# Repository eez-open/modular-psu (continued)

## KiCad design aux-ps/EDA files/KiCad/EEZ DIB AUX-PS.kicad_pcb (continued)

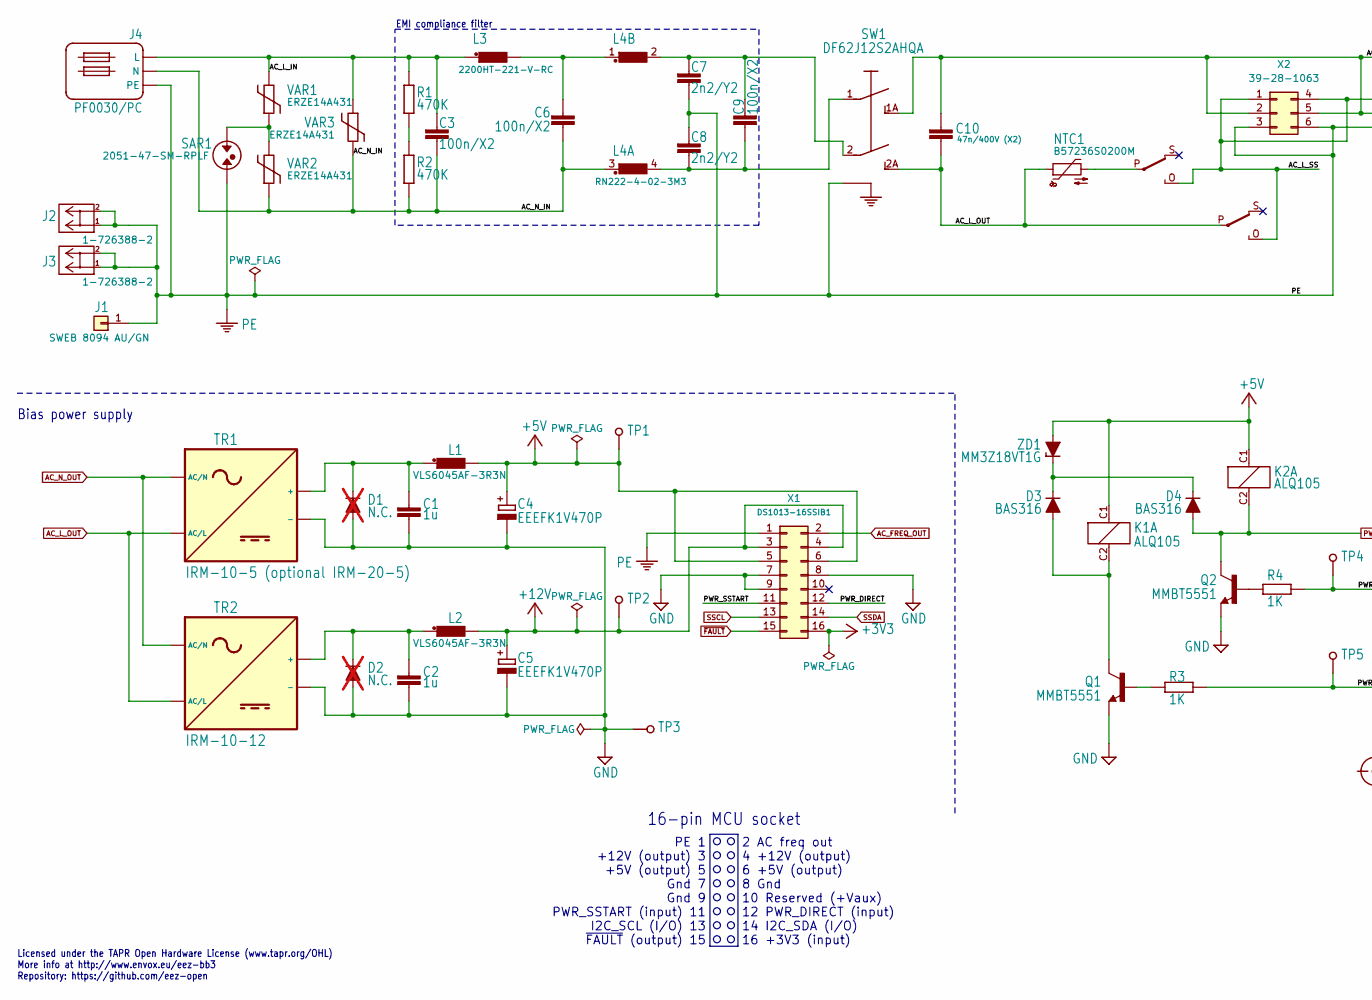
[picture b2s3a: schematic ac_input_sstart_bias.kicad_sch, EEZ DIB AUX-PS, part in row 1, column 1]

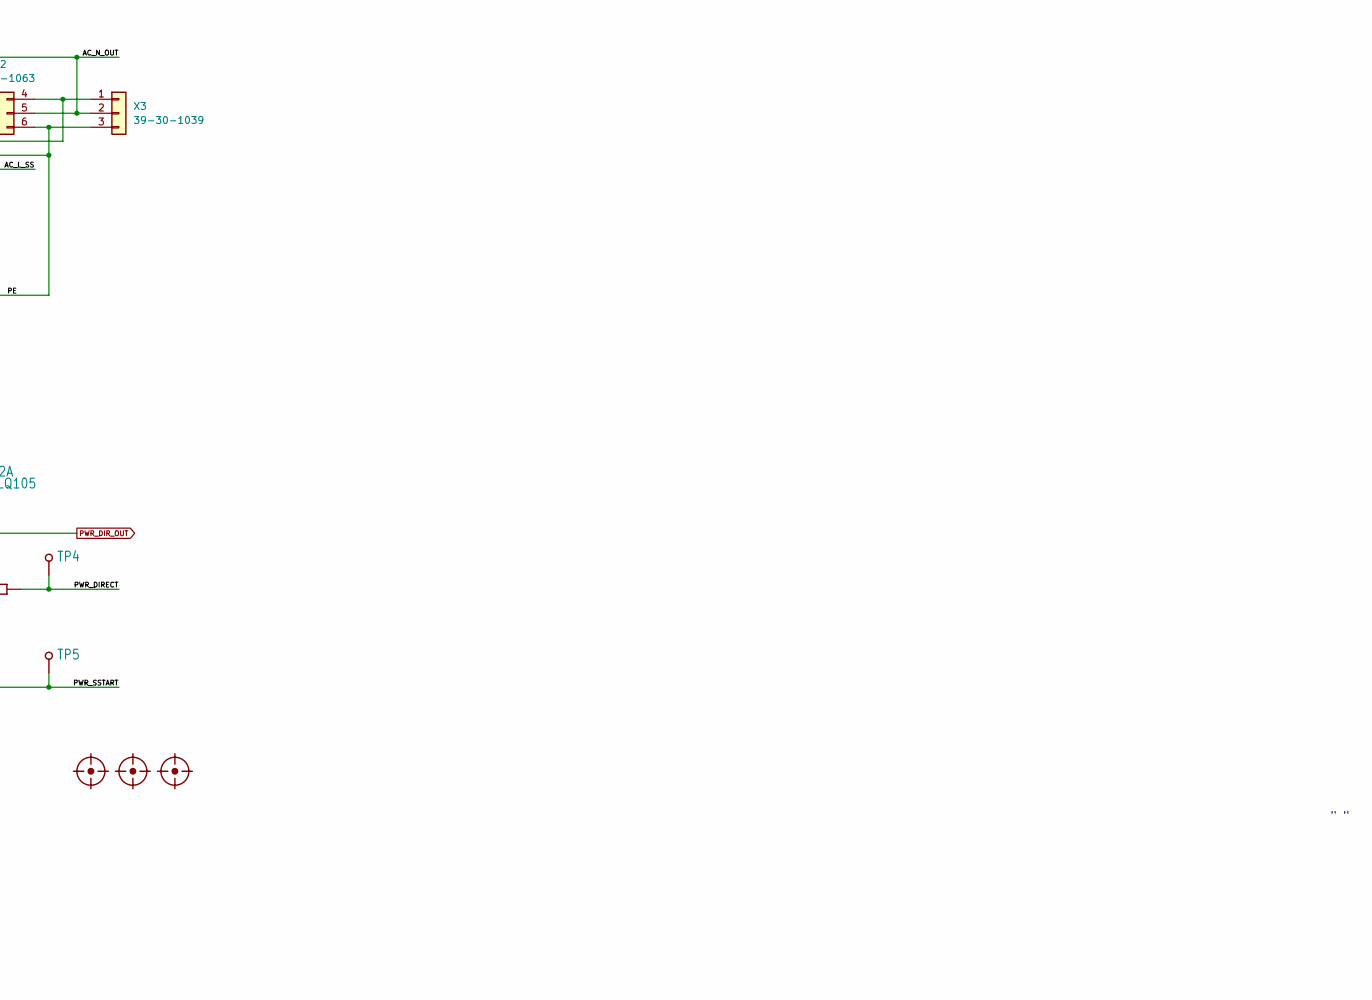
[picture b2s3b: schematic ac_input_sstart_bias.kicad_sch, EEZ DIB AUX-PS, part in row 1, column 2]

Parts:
C1, C2: 1u; C_0805_2012Metric; DigiKey 490-10494-2-ND
C3, C6, C9: 100n/X2; C150-054X183; DigiKey 399-6806-ND
C4, C5: EEEFK1V470P; CAPAE660X610N; DigiKey PCE3842CT-ND
C7, C8: 2n2/Y2; C075-042X103; DigiKey 495-4874-1-ND
C10: 47n/400V (X2); C102-054X133; DigiKey 399-11478-ND
D1, D2: N.C.; DO214AA; not fitted
D3, D4: BAS316; SOD-323_1P8X1P35_ONS-M; DigiKey 1727-7370-1-ND
FM1, FM2, FM3: FIDUCIAL; Fiducial
J1: SWEB 8094 AU/GN; SWEB 8094_AU_GN
J2, J3: 1-726388-2; DigiKey 1-726388-2-ND
J4: PF0030/PC; PF0030_PC; DigiKey 708-1914-ND
K1, K2: ALQ105; PAN_ALQ1XX; DigiKey 255-3565-ND
L1, L2: VLS6045AF-3R3N; COILCRAFT_HPI0630; DigiKey 445-180834-1-ND
L3: 2200HT-221-V-RC; BOURNS_2200; DigiKey 2200HT-221-V-RC-ND
L4: RN222-4-02-3M3; BOURNS_7100_COMBO; DigiKey 817-2100-ND
NTC1: B57236S0200M; NTC_11.5X6_RM5; DigiKey 495-3047-ND
Q1, Q2: MMBT5551; SOT23-BEC; DigiKey 4878-MMBT5551CT-ND
R1, R2: 470K; R_0805_2012Metric; DigiKey A126370CT-ND
R3, R4: 1K; R_0805_2012Metric; DigiKey 311-1.00KCRTR-ND
SAR1: 2051-47-SM-RPLF; SAR_4.5MM; DigiKey 2051-47-SM-RPLFCT-ND
SW1: DF62J12S2AHQA; DF62J12S2; DigiKey CKN2062-ND
TP1, TP2, TP3, TP4, TP5: PCB_TEST_TABSHIELD; Testhole 24_50mils
TR1: IRM-10-5 (optional IRM-20-5); IRM-10_20_COMBO; DigiKey 1866-3032-ND
TR2: IRM-10-12; IRM-10; DigiKey 1866-3028-ND
VAR1, VAR2, VAR3: ERZE14A431; VARISTOR_14MM_RM7.5MM; DigiKey P16688-ND
X1: DS1013-16SSIB1; ZL231-16PG; DigiKey ED10523-ND
X2: 39-28-1063; MINIFIT_5566-06A_CRE; DigiKey WM3802-ND
X3: 39-30-1039; MINIFIT_39301039_CRE; DigiKey WM18442-ND
ZD1: MM3Z18VT1G; SOD-323_1P8X1P35_ONS-M; DigiKey MM3Z18VT1GOSCT-ND

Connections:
+3V3: X1.16; also elsewhere on the board
+5V: C4.+, K1.C1, K2.C1, L1.2, TP1.1, X1.5, X1.6, ZD1.A; also elsewhere on the board
+12V: C5.+, L2.2, TP2.1, X1.3, X1.4; also elsewhere on the board
/AC input, soft start and bias power/AC_L_IN: C3.1, J4.L, L3.1, R1.2, VAR1.2, VAR3.1
/AC input, soft start and bias power/AC_L_SS: K1.O, K2.O, X2.1, X2.4, X3.1
/AC input, soft start and bias power/AC_N_IN: C3.2, C6.2, J4.N, L4.3 (1), R2.1, VAR2.1, VAR3.2
/AC input, soft start and bias power/PWR_DIRECT: R4.2, TP4.1, X1.12
/AC input, soft start and bias power/PWR_SSTART: R3.2, TP5.1, X1.11
AC_FREQ_OUT: X1.2; also elsewhere on the board
AC_L_OUT: C10.2, K2.P, NTC1.1, SW1.2A (S1), TR1.ACL (AC/L), TR2.ACL (AC/L); also elsewhere on the board
AC_N_OUT: C10.1, SW1.1A (S), TR1.ACN (AC/N), TR2.ACN (AC/N), X2.2, X2.5, X3.2; also elsewhere on the board
GND: C1.2, C2.2, C4.-, C5.-, D1.A, D2.A, Q1.E, Q2.E, TP3.1, TR1.V- (-), TR2.V- (-), X1.7, X1.8, X1.9; also elsewhere on the board
unnamed: C6.1, L3.2, L4.1
unnamed: D3.A, K1.C2, Q1.C
unnamed: D3.C, D4.C, ZD1.C
unnamed: K1.P, NTC1.2
unnamed: C8.2, C9.1, L4.4 (2), SW1.1
unnamed: Q1.B, R3.1
unnamed: Q2.B, R4.1
unnamed: R1.1, R2.2
unnamed: SAR1.1, VAR1.1, VAR2.2
unnamed: C7.1, C9.2, L4.2, SW1.2 (P1)
unnamed: C1.1, D1.C, L1.1, TR1.V+ (+)
unnamed: C2.1, D2.C, L2.1, TR2.V+ (+)
PE: C7.2, C8.1, J1.1, J2.1, J2.2, J3.1, J3.2, J4.PE, SAR1.2, SW1.PE, X1.1, X2.3, X2.6, X3.3; also elsewhere on the board
PWR_DIR_OUT: D4.A, K2.C2, Q2.C; also elsewhere on the board
SSCL: X1.13; also elsewhere on the board
SSDA: X1.14; also elsewhere on the board
~FAULT: X1.15; also elsewhere on the board

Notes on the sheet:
2 AC freq out 4 +12V (output) 6 +5V (output) 8 Gnd 10 Reserved (+Vaux) 12 PWR_DIRECT (input) 14 I2C_SDA (I/O) 16 +3V3 (input)
PE 1 +12V (output) 3 +5V (output) 5 Gnd 7 Gnd 9 PWR_SSTART (input) 11 I2C_SCL (I/O) 13 ~{FAULT} (output) 15
EMI compliance filter
" "
Bias power supply
16-pin MCU socket
Licensed under the TAPR Open Hardware License (www.tapr.org/OHL) More info at http://www.envox.eu/eez-bb3 Repository: https://github.com/eez-open

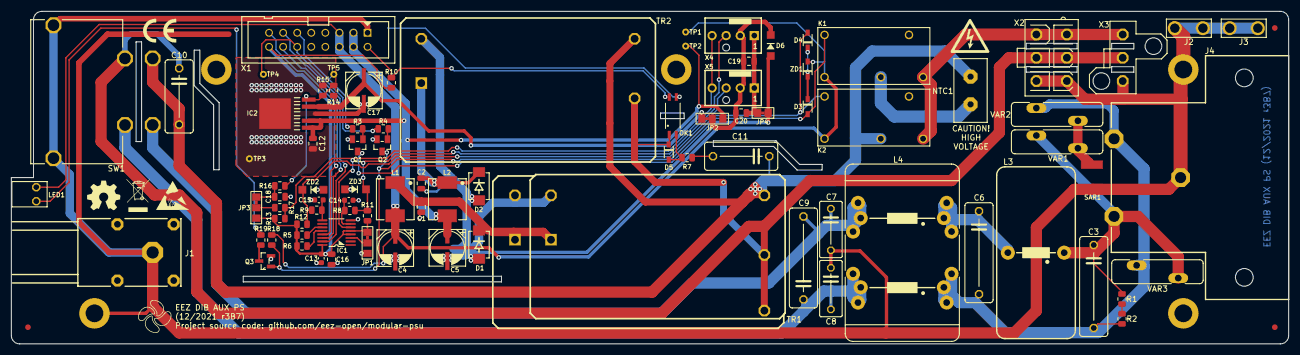
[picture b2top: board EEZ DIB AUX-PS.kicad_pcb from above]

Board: 2 copper layers, 230.5 x 60.0 mm, 101 parts (0 on the bottom side), 47 nets.

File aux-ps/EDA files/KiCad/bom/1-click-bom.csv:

References,Qty,Description,Manufacturer,MPN,Manufacturer,MPN,Manufacturer,MPN,DigiKey,Mouser,TME
"C1, C2, C16, C18, C19",5,1u,,490-10494-2-ND,,81-GRM219R7YA105KA2J,,GRM219R7YA105KA12D,,,
C10,1,47n/400V (X2),,399-11478-ND,,871-B32921C3473K,,MKP-X2-47NR10/310,,,
"C13, C14",2,100n,,1276-1005-2-ND,,187-CL10B104KO8NNNC ,,CL10B104KA8NNNC,,,
"C3, C6, C9",3,100n/X2,,399-6806-ND ,,80-R46KI310000M1M,,R46KI310000M1M,,,
"C4, C5, C17",3,EEEFK1V470P,,PCE3842CT-ND,,667-EEE-FK1V470P,,EEEFK1V470P,,,
"C7, C8",2,2n2/Y2,,495-4874-1-ND,,871-B32620A6222J289,,R66PD1220AA10K,,,
"D3, D4",2,BAS316,,1727-7370-1-ND,,771-BAS316-T/R,,"BAS316,115",,,
D6,1,SKL14,,1727-7335-1-ND,,841-PMEG4010EGWX,,SKL14-DIO,,,
IC1,1,MAX31760AEE+,,MAX31760AEE+-ND ,,700-MAX31760AEE+,,-,,,
IC2,1,BD00FC0W,,BD00FC0WFP-E2TR-ND,,755-BD00FC0WFP-E2,,-,,,
J1,1,SWEB 8094 AU/GN,,-,,-,,SWEB 8094 AU/GN,,,
"J2, J3",2,1-726388-2,,1-726388-2-ND,,571-1-726388-2,,61-1560-21/0030,,,
J4,1,PF0030/PC,,708-1914-ND,,161-PF0030/PC,,PF0030/PC,,,
"K1, K2",2,ALQ105,,255-3565-ND,,769-ALQ105,,ALQ105,,,
"L1, L2",2,VLS6045AF-3R3N,,445-180834-1-ND,,810-VLS6045AF-3R3N,,HPI0630-3R3,,,
L3,1,2200HT-221-V-RC,,2200HT-221-V-RC-ND,,542-2200HT-221V-RC,,-,,,
L4,1,RN222-4-02-3M3,,817-2100-ND,,631-RN112-4-02-0M7,,-,,,
LED1,1,WP934CB/YD,,754-1300-ND,,604-WP934CB/YD ,,L-934CB/1YD,,,
NTC1,1,B57236S0200M,,495-3047-ND ,,871-B57236S200M,,B57236S0200,,,
"Q1, Q2",2,MMBT5551,,4878-MMBT5551CT-ND,,863-MMBT5551LT1G,,MMBT5551-7-F,,,
Q3,1,2N7002,,T2N7002AKLMCT-ND,,757-T2N7002AKLM,,2N7002LT1G,,,
"R1, R2",2,470K,,A126370CT-ND,,71-CRCW0805470KFKEA,,0805S8J0474T5E,,,
"R14, R18",2,39K,,RMCF0805FT39K0CT-ND,,652-CR0805FX-3902ELF,,0805S8J0393T5E,,,
"R15, R16",2,3K3,,A129755CT-ND,,603-RC0805FR-073K3L,,805S8F3301T5E,,,
R19,1,470R,,311-470CRCT-ND,,71-CRCW0805470RFKEB,,RC0805FR-07470R,,,
"R3, R4, R11, R12, R17",5,1K,,311-1.00KCRTR-ND,,603-RC0805FR-071KL,,RC0805FR-071K,,,
"R5, R13",2,4K7,,311-4.70KCRCT-ND,,603-RC0805FR-074K7L,,0805S8F4701T5E,,,
R8,1,10R,,311-10.0CRTR-ND,,652-CR0805AFX10R0EAS,,SMD0805-10R-1%,,,
SAR1,1,2051-47-SM-RPLF,,2051-47-SM-RPLFCT-ND,,652-2051-47-SM-RPLF,,-,,,
SW1,1,DF62J12S2AHQA,,CKN2062-ND,,611-DF62J12S2AHQA,,DF62J12S2AHQA,,,
TR1,1,IRM-10-5 (optional IRM-20-5),,1866-3032-ND,,709-IRM10-5 ,,IRM-10-5,,,
TR2,1,IRM-10-12,,1866-3028-ND ,,709-IRM10-12 ,,IRM-10-12,,,
"VAR1, VAR2, VAR3",3,ERZE14A431,,P16688-ND,,667-ERZ-E11A431,,V275LA20AP,,,
X1,1,DS1013-16SSIB1,,ED10523-ND,,710-61201621621,,DS1013-16SSIB1,,,
X2,1,39-28-1063,,WM3802-ND,,538-39-28-1063,,MX-5566-06A,,,
X3,1,39-30-1039,,WM18442-ND ,,538-39-30-1039 ,,MX-5566-03A3,,,
X4,1,22-27-2031,,WM4112-ND,,538-22-27-2031,,MX-6410-03A,,,
ZD1,1,MM3Z18VT1G,,MM3Z18VT1GOSCT-ND,,863-MM3Z18VT1G,,MM3Z18VT1G,,,

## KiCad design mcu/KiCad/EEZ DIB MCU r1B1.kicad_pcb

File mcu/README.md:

### Overview

_IMPORTANT: A crowdfunded version of the MCU module (r2B4) can be found [here](https://github.com/eez-open/modular-psu/tree/master/previous%20designs/mcu%20r2B4%20(Crowd%20Supply%20edition))._

STM32F7 MCU board for controlling up to 3 SPI peripheral modules, I2C fan controller, power soft-start/standby, TFT LCD with resistive touch controller, USB OTG, 10/100 Mbit/s Ethernet, SDRAM, EEPROM, rotary encoder, user switch, speaker and 2+2 digital I/O.

### r3B3 prototype

### Feature list

* [STM32F769IIT6](https://www.st.com/content/st_com/en/products/microcontrollers-microprocessors/stm32-32-bit-arm-cortex-mcus/stm32-high-performance-mcus/stm32f7-series/stm32f7x9/stm32f769ii.html) 32-bit ARM Cortex®-M7 MCU, 216 MHz, 2 MiB Flash, 512 KiB SRAM,  LQFP176 package
* Digital I/O: 2 x buffered inputs and 2 x buffered outputs. Alternative functions: UART, 1 x PWM
* Rotary encoder with switch
* 1 x user switch (use as BOOT0 for firmware loader on power up)
* 3 x SPI channels (2 x Chip selects per channel), 40-pin IDC connector (DIB v1.0)
* Battery backup (CR2032 button cell type)
* AC frequency (50/60 Hz) RTC reference (optional)
* External supervisor with watchdog (optional)
* USB FS, OTG
* Micro SD card
* [DP83848C](https://www.ti.com/product/DP83848C) Ethernet PHY (10/100 Mbit/s)
* 32 KiB I2C EEPROM
* SWG/JTAG connector (optional)
* 8 MiB SDRAM (e.g. [IS42S16400J](https://www.tme.eu/en/details/is42s16400j-7tli/dram-memories-integrated-circuits/issi/)) upgradeable to 32 MiB
* 0.5 mm FFC 40-pin connector for 4.3" TFT LCD 480 x 272 px display
* TFT backlight brightness control
* Resistive touch controller (I2C)
* Soft-start/stand-by control lines for [AUX PS board](https://github.com/eez-open/modular-psu/tree/master/aux-ps)
* Small on-board speaker
* Input power: +5 V (+12 V pass-thru to peripheral modules)
* On board +3.3 V LDO
* Dimensions: 139.5 x 70 mm, 4-layer PCB
* **CE certified design**

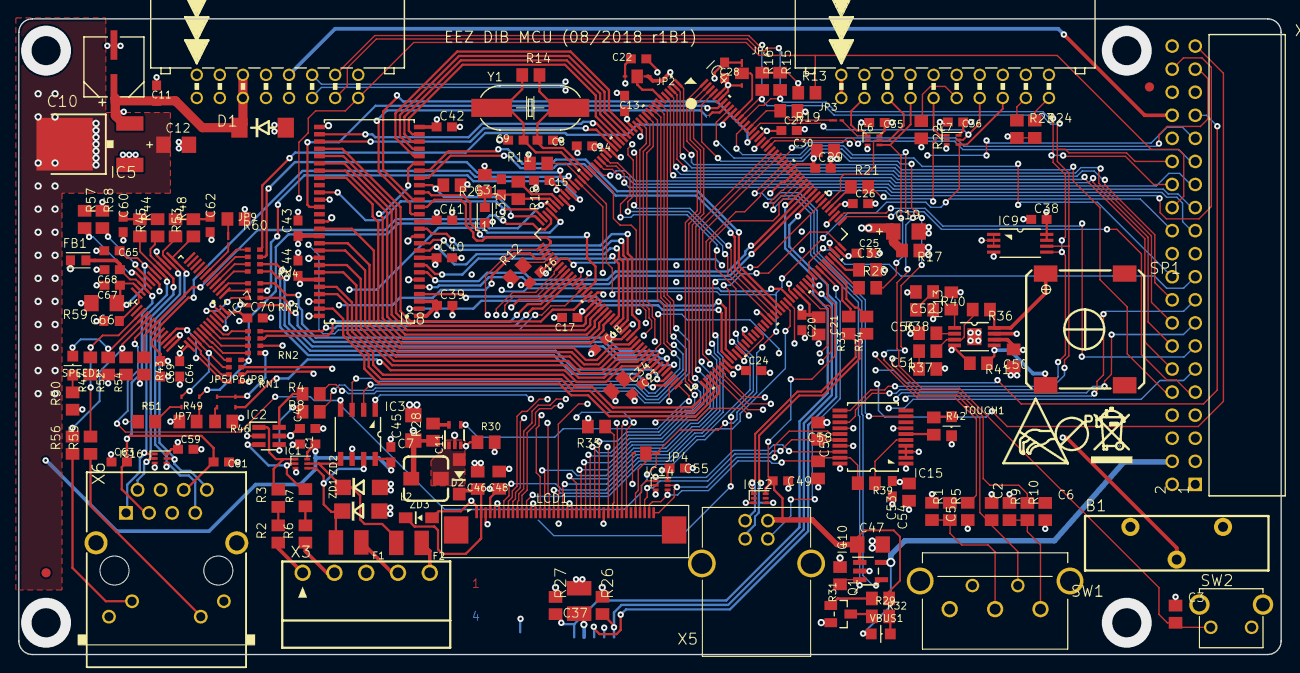
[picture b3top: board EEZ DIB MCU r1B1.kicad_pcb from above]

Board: 4 copper layers, 139.0 x 70.0 mm, 193 parts (0 on the bottom side), 233 nets.

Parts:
B1: DS1092-16-B6P
C1, C4, C7, C11, C13, C14, C15, C16, C17, C18, C20, C23, C24, C25, C26, C27, C28, C29, C32, C35, C36, C38, C39, C40, C41, C42, C43, C44, C49, C53, C55, C59, C60, C61, C62, C63, C64, C65, C67, C68, C69, C70: 100n; C0603
C2, C3, C5, C6, C57, C58: 10n; C0805
C8, C9: 18p; C0603
C10: 47u; CAPAE660X610N
C12, C66: 10u; EC1206
C19: 4u7; EC1206
C21, C30, C31, C46, C50, C54: 1u; C0805
C22: N.C.; C0603
C33, C34, C48: 2u2; C0805
C37: 10u; C1210
C45: 4u7; C1206
C47: 4u7/16V (293D475X9016A2TE3); EC1206
C51, C52: 470n; C0805
C56: 220n; C0805
D1: SMBJ5.0A-TR; DO214AA
D2: NSR0240; SOD123
EEZ_SIGNATURE: SIGNATURESMALL; SIGNATURE_5MM
F1, F2: 50mA; F1210
FB1: 60R@100MHz; BEAD0603
FM1, FM2: FIDUCIAL
IC1, IC6, IC7, IC12, IC14, IC16: TPD4E001DRLR; DRL6
IC2: SN74LVC2G34DBVR; DBV6
IC3: BTS3408G; SOIC127P600X173-8N
IC4: STM32F769IGT6; LQFP-176_24X24MM
IC5: LD1117ADT33TR; DPACK
IC8: IS42S16400J; TSOPII-54
IC9: BR24G64FVT-3AGE2; PW8_TSSOP8
IC10: TPS2051BDBVR; DBV5
IC11: TPS61169DCKR; DCK5
IC13: TPA6205A1DGN; SOP65P490X110-9N
IC15: AR1021-I/SS; SOP65P780X200-20N
IC17: DP83848CVV_NOPB; PT48
J1: 5033981892
JP1, JP2, JP4: JP3-CUT
JP3, JP9: JP2-NOCUT
JP5, JP6, JP7, JP8: JP2-CUT
L1: LCBA-600; BEAD0603
L2: DLG-0403-4R7; DE0403
LCD1: PCA-6-LA-40-HL-3; FPC_40
Q1: MMBT5551; SOT23-BEC
R1, R2, R3, R6, R7, R9, R13, R15, R16, R42: 4K7; R0805
R4, R8: 1K; R0805
R5, R10, R11, R12, R22, R23, R24, R25, R35, R37, R38: 10K; R0805
R14: 1M; R0805
R17: 0R; R0805
R18: 47R; R0805
R19, R26, R27, R29, R31, R32, R40: 47K; R0805
R20, R21, R33, R34: 22R; R0805
R28, R30: 10R; R0805
R36, R39, R41: 20K; R0805
R43: 1K5; R0805
R44, R45, R48, R53: 49R9; R0805
R46, R47, R49, R51, R52, R54, R57, R58, R60: 2K2; R0805
R50, R55, R56: 220R; R0805
R59: 4K87; R0603
RN1, RN2, RN3, RN4: DR1206-33R-4/8; CAY16
SP1: LD-BZEL-M1313
SPEED1: HSMY-C170; LED_0805
SW1: PEC16-2215F-S0024; PEC16-2215F
SW2: BSF-3152; BSF-315X
TOUCH1: HSMY-C170; LED_0805
U$1: RECYCLE_BIN1_8
U$5: PB_SMALL
U$6: ESD_SYMBOL
VBUS1: HSMG-C170; LED_0805
X1: ZL263-40DG
X2: ZL231-16KG; ML16L
X3: 1844249; MC1,5_5-G-3,5
X4: ZL231-20KG; ML20L
X5: 292304-1; USB-B
X6: LMJTAB881243M-L; RJ45-TRAFO-LED
Y1: 10MHz; HC-49_4H
ZD1, ZD2: SMAJ18A; DO214AC
ZD3: BZX384-B30.115; SOD323-W

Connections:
+3V3: C4.1, C12.+, C35.1, C36.1, C37.1, C38.2, C39.1, C40.1, C41.1, C42.1, C43.1, C44.1, C45.1, C48.1, C50.2, C53.2, C54.2, C55.2, C59.1, C69.1, C70.1, FB1.P$1, IC2.5, IC5.4, IC6.6, IC7.6, IC8.1, IC8.3, IC8.9, IC8.14, IC8.27, IC8.43, IC8.49, IC9.1, IC9.2, IC9.3, IC9.7, IC9.8, IC13.6, IC14.6, IC15.1, IC16.6, IC17.32, IC17.48, J1.4, L2.1, LCD1.4, R1.1, R9.1, R13.1, R15.1, R16.1, R17.1, R19.1, R25.1, R26.1, R27.1, R28.1, R31.2, R35.2, R40.2, R43.2, R47.1, R50.1, R51.1, R52.1, R54.1, R57.1, R58.1, R60.1, X1.32, X2.16, X4.1, X4.2, X6.9, X6.12
+3V3(A): C61.2, C63.2, C68.1, FB1.P$2, IC17.22, X6.3, X6.6
+5V: C1.1, C7.2, C10.1, C11.1, D1.C, IC1.6, IC3.8, IC5.3, IC10.5, VBUS1.A, X1.3, X1.4, X2.5, X2.6
+12V: X1.5, X1.6, X2.3, X2.4
/Ethernet PHY/LED_ACT: IC17.26, R47.2, R55.2
/Ethernet PHY/LED_LINK: IC17.28, R54.2, R56.2
/Ethernet PHY/LED_SPEED: IC17.27, R52.2, SPEED1.C
/I/O connectors, encoders, user SW/+VAUX: X1.34, X2.10
/SDRAM, JTAG, SD card, EEPROM/DBGACK: R24.1, X4.19
/SDRAM, JTAG, SD card, EEPROM/DBGRQ: R23.1, X4.17
/SDRAM, JTAG, SD card, EEPROM/RTCK: R22.1, X4.11
/SDRAM, JTAG, SD card, EEPROM/TCK: IC7.1, R21.2, X4.9
/SDRAM, JTAG, SD card, EEPROM/TMS: IC6.4, R20.2, X4.7
/STM32F7 MCU/BOOT0: IC4.166, JP1.COM
/STM32F7 MCU/BYPASS_REG: IC4.48, R12.2
/STM32F7 MCU/RCC_OSC_IN: C8.2, IC4.29, R14.2, Y1.2
/STM32F7 MCU/RCC_OSC_OUT: C9.2, IC4.30, R14.1, Y1.1
/STM32F7 MCU/VBAT: IC4.6, JP2.COM
/STM32F7 MCU/VCAP1: C34.1, IC4.81
/STM32F7 MCU/VCAP2: C33.1, IC4.129
/STM32F7 MCU/VDDA: C31.1, C32.1, IC4.39, L1.P$2, R18.2
/STM32F7 MCU/VREF+: IC4.38, R18.1
/TFT, Audio, USB/LCD_DISP: LCD1.31, R35.1
/TFT, Audio, USB/USB_D_N: IC12.1, R33.1, X5.2
/TFT, Audio, USB/USB_D_P: IC12.4, R34.1, X5.3
/TFT, Audio, USB/VLED+: C46.1, D2.C, LCD1.2, ZD3.C
/TFT, Audio, USB/VLED-: IC11.3, LCD1.1, R30.1, ZD3.A
/TFT, Audio, USB/~AUDIO_SHDN: IC13.1, R40.1
DAC_OUT1: C52.2, IC4.50
DIN1: IC4.7, R4.2
DIN2: IC4.8, R8.2
DOUT1: IC3.2, IC4.9
DOUT2: IC3.3, IC4.10
ENC_A: C5.2, IC4.119, R5.1
ENC_B: C6.1, IC4.120, R10.1
ENC_SW: C2.2, IC4.173, SW1.E
ETH_COL: IC4.47, RN2.2
ETH_CRS: IC4.40, JP5.1, RN1.4
ETH_MDC: IC4.33, IC17.31
ETH_MDIO: IC4.42, IC17.30, R43.1
ETH_RXD0: IC4.54, RN2.3
ETH_RXD1: IC4.55, RN2.4
ETH_RXD2: IC4.83, RN3.1
ETH_RXD3: IC4.84, RN3.2
ETH_RX_CLK: IC4.41, RN1.2
ETH_RX_DV: IC4.53, RN1.3
ETH_TXD0: IC4.85, RN4.1
ETH_TXD1: IC4.86, RN4.2
ETH_TXD2: IC4.34, RN4.3
ETH_TXD3: IC4.167, RN4.4
ETH_TX_CLK: IC4.35, RN3.3
ETH_TX_EN: IC4.80, RN3.4
FMC_A0: IC4.16, IC8.23
FMC_A1: IC4.17, IC8.24
FMC_A2: IC4.18, IC8.25
FMC_A3: IC4.19, IC8.26
FMC_A4: IC4.20, IC8.29
FMC_A5: IC4.21, IC8.30
FMC_A6: IC4.60, IC8.31
FMC_A7: IC4.63, IC8.32
FMC_A8: IC4.64, IC8.33
FMC_A9: IC4.65, IC8.34
FMC_A10: IC4.66, IC8.22
FMC_A11: IC4.67, IC8.35
FMC_BA0: IC4.112, IC8.20
FMC_BA1: IC4.113, IC8.21
FMC_D0: IC4.97, IC8.2
FMC_D1: IC4.98, IC8.4
FMC_D2: IC4.142, IC8.5
FMC_D3: IC4.143, IC8.7
FMC_D4: IC4.68, IC8.8
FMC_D5: IC4.69, IC8.10
FMC_D6: IC4.70, IC8.11
FMC_D7: IC4.73, IC8.13
FMC_D8: IC4.74, IC8.42
FMC_D9: IC4.75, IC8.44
FMC_D10: IC4.76, IC8.45
FMC_D11: IC4.77, IC8.47
FMC_D12: IC4.78, IC8.48
FMC_D13: IC4.89, IC8.50
FMC_D14: IC4.90, IC8.51
FMC_D15: IC4.91, IC8.53
FMC_NBL0: IC4.169, IC8.15
FMC_NBL1: IC4.170, IC8.39
FMC_SDCKE0: IC4.43, IC8.37
FMC_SDCLK: IC4.116, IC8.38
FMC_SDNCAS: IC4.160, IC8.17
FMC_SDNE0: IC4.44, IC8.19, R25.2
FMC_SDNRAS: IC4.59, IC8.18
FMC_SDNWE: IC4.46, IC8.16
GND: B1.1, B1.3, C1.2, C2.1, C3.1, C4.2, C5.1, C6.2, C7.1, C8.1, C9.1, C10.2, C11.2, C12.-, C13.2, C14.2, C15.2, C16.2, C17.2, C18.2, C19.-, C20.2, C21.2, C22.2, C23.2, C24.2, C25.2, C26.2, C27.2, C28.2, C29.2, C30.2, C31.2, C32.2, C33.2, C34.2, C35.2, C36.2, C37.2, C38.1, C39.2, C40.2, C41.2, C42.2, C43.2, C44.2, C45.2, C46.2, C47.-, C48.2, C49.1, C50.1, C51.2, C53.1, C54.1, C55.1, C56.1, C57.2, C58.2, C59.2, C60.2, C61.1, C62.2, C63.1, C64.2, C65.2, C66.-, C67.2, C68.2, C69.2, C70.2, D1.A, IC1.3, IC2.2, IC3.6, IC4.14, IC4.22, IC4.37, IC4.61, IC4.71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
I2C1_SCL: IC4.164, IC9.5, IC15.11, R15.2, X1.28, X2.13
I2C1_SDA: IC4.165, IC9.6, IC15.13, R16.2, X1.30, X2.14
IRQ_TOUCH: IC4.151, IC15.9
LTDC_B2: IC4.150, LCD1.23
LTDC_B3: IC4.154, LCD1.24
LTDC_B4: IC4.155, LCD1.25
LTDC_B5: IC4.174, LCD1.26
LTDC_B6: IC4.175, LCD1.27
LTDC_B7: IC4.176, LCD1.28
LTDC_CLK: IC4.115, LCD1.30
LTDC_DE: IC4.28, LCD1.34
LTDC_G2: IC4.52, LCD1.15
LTDC_G3: IC4.153, LCD1.16
LTDC_G4: IC4.45, LCD1.17
LTDC_G5: IC4.132, LCD1.18
LTDC_G6: IC4.13, LCD1.19
LTDC_G7: IC4.145, LCD1.20
LTDC_HSYNC: IC4.12, LCD1.32
LTDC_R2: IC4.139, LCD1.7
LTDC_R3: IC4.56, LCD1.8
LTDC_R4: IC4.51, LCD1.9
LTDC_R5: IC4.32, LCD1.10
LTDC_R6: IC4.57, LCD1.11
LTDC_R7: IC4.114, LCD1.12
LTDC_VSYNC: IC4.11, LCD1.33
MCLK_25: IC4.122, RN1.1
unnamed: B1.2, JP2.NC
unnamed: C51.1, R37.2
unnamed: C52.1, R38.2
unnamed: C56.2, IC13.2
unnamed: C57.1, IC14.4, IC15.19, LCD1.39, R39.2
unnamed: C58.1, IC14.2, IC15.16, LCD1.38
unnamed: C60.1, R44.1, R45.2
unnamed: C62.1, R48.1, R53.2
unnamed: C64.1, C65.1, C66.+, C67.1, IC17.18, IC17.23, IC17.37
unnamed: D2.A, IC11.1, L2.2
unnamed: F1.1, X3.4
unnamed: F1.2, IC1.4, IC3.7, ZD1.C
unnamed: F2.1, X3.5
unnamed: F2.2, IC1.5, IC3.5, ZD2.C
unnamed: IC1.1, IC2.1, R3.2
unnamed: IC1.2, IC2.3, R7.2
unnamed: IC2.4, R8.1
unnamed: IC2.6, R4.1
unnamed: IC4.100, IC4.106
unnamed: IC6.1, JP3.2, X4.3
unnamed: IC11.5, R28.2
unnamed: IC13.3, R36.2, R37.1
unnamed: IC13.4, R38.1, R41.2
unnamed: IC13.5, R41.1, SP1.-
unnamed: IC13.8, R36.1, SP1.+
unnamed: IC14.1, IC15.18, LCD1.37
unnamed: IC14.5, IC15.15, LCD1.40
unnamed: IC15.5, R39.1
unnamed: IC15.6, R42.2
unnamed: IC16.1, IC17.17, R44.2, X6.1
unnamed: IC16.2, IC17.16, R45.1, X6.2
unnamed: IC16.4, IC17.14, R48.2, X6.7
unnamed: IC16.5, IC17.13, R53.1, X6.8
unnamed: IC17.1, RN3.6
unnamed: IC17.2, RN3.5
unnamed: IC17.3, RN4.8
unnamed: IC17.4, RN4.7
unnamed: IC17.5, RN4.6
unnamed: IC17.6, RN4.5
unnamed: IC17.7, JP9.2
unnamed: IC17.20, R58.2
unnamed: IC17.21, R57.2
unnamed: IC17.24, R59.2
unnamed: IC17.34, RN1.8
unnamed: IC17.38, RN1.7
unnamed: IC17.39, JP7.2, RN1.6
unnamed: IC17.40, RN1.5
unnamed: IC17.41, RN2.8
unnamed: IC17.42, RN2.7
unnamed: IC17.43, RN2.6
unnamed: IC17.44, RN2.5
unnamed: IC17.45, RN3.8
unnamed: IC17.46, RN3.7
unnamed: JP4.COM, LCD1.36
unnamed: JP5.2, R49.2
unnamed: JP6.1, JP8.1, RN2.1
unnamed: JP6.2, R46.2
unnamed: JP7.1, R51.2
unnamed: JP9.1, R60.2
unnamed: Q1.B, R32.2
unnamed: Q1.C, R29.1
unnamed: R1.2, R5.2, SW1.B
unnamed: R2.1, X3.1
unnamed: R2.2, R3.1
unnamed: R6.1, X3.2
unnamed: R6.2, R7.1
unnamed: R9.2, R10.2, SW1.A
unnamed: R29.2, VBUS1.C
unnamed: R42.1, TOUCH1.A
unnamed: R50.2, SPEED1.A
unnamed: R55.1, X6.11
unnamed: R56.1, X6.10
OE_SYNC: IC4.94, X1.39
OUT_PAR: IC4.140, X1.38
OUT_SER: IC4.152, X1.37
PE: X2.1, X2.2, X5.M1, X5.M2, X6.SH, X6.SH2
PWR_DIRECT: IC4.110, X2.12
PWR_SSTART: IC4.111, X2.11
SDMMC1_CK: IC4.141, J1.5
SDMMC1_CMD: IC4.144, J1.3, R27.2
SDMMC1_D0: IC4.121, J1.7, R26.2
SD_DETECT: IC4.24, J1.SW1
SPI2_CLK: IC4.133, X1.9
SPI2_CSA: IC4.93, X1.15
SPI2_CSB: IC4.92, X1.17
SPI2_IRQ: IC4.123, X1.19
SPI2_MISO: IC4.87, X1.11
SPI2_MOSI: IC4.134, X1.13
SPI4_CLK: IC4.1, X1.10
SPI4_CSA: IC4.2, X1.16
SPI4_CSB: IC4.3, X1.18
SPI4_IRQ: IC4.168, X1.20
SPI4_MISO: IC4.4, X1.12
SPI4_MOSI: IC4.5, X1.14
SPI5_CLK: IC4.25, X1.23
SPI5_CSA: IC4.157, X1.29
SPI5_CSB: IC4.156, X1.31
SPI5_IRQ: IC4.79, JP8.2, X1.33
SPI5_MISO: IC4.26, X1.25
SPI5_MOSI: IC4.27, X1.27
SYS_JTCK-SWCLK: IC4.137, R21.1
SYS_JTDI: IC4.138, IC6.5, X4.5
SYS_JTDO-SWO: IC4.161, IC7.5, X4.13
SYS_JTMS-SWDIO: IC4.128, R20.1
SYS_JTRST: IC4.162, JP3.1, R19.2
TFT_BRIGHTNESS: IC4.88, IC11.4
USB_OTG_FS_D_N: IC4.126, R33.2
USB_OTG_FS_D_P: IC4.127, R34.2
USB_OTG_FS_ID: IC4.125, X5.4
USB_OTG_FS_PSO: IC4.147, IC10.4
USB_OTG_FS_VBUS: C47.+, C49.2, IC4.124, IC10.1, IC12.6, R32.1, X5.1
USER_SW: C3.2, IC4.163, SW2.1
VDD: C13.1, C14.1, C15.1, C16.1, C17.1, C18.1, C19.+, C20.1, C21.1, C22.1, C23.1, C24.1, C25.1, C26.1, C27.1, C28.1, C29.1, C30.1, IC4.15, IC4.23, IC4.36, IC4.49, IC4.62, IC4.72, IC4.82, IC4.96, IC4.99, IC4.118, IC4.131, IC4.136, IC4.149, IC4.159, IC4.171, IC4.172, JP1.NO, JP2.NO, L1.P$1, R11.1, R17.2
~FAULT: IC3.1, IC4.58, R13.2, X1.26, X2.15
~RESET: IC3.4, IC4.31, IC7.4, IC17.29, JP4.NC, R11.2, X1.24, X4.15
~USB_OTG_FS_OC: IC4.146, IC10.3, R31.1

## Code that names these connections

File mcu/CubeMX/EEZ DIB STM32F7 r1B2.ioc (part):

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Mcu.Name=STM32F769IGTx
Mcu.Package=LQFP176
Mcu.UserName=STM32F769IGTx
PA0/WKUP.Mode=MII
PA0/WKUP.Signal=ETH_CRS
PA1.Mode=MII
PA1.Signal=ETH_RX_CLK
PA10.Mode=OTG/Dual_Role_Device
PA10.Signal=USB_OTG_FS_ID
PA11.Mode=OTG/Dual_Role_Device
PA11.Signal=USB_OTG_FS_DM
PA12.Mode=OTG/Dual_Role_Device
PA12.Signal=USB_OTG_FS_DP
PA13.Mode=Trace_Asynchronous_SW
PA13.Signal=SYS_JTMS-SWDIO
PA14.Mode=Trace_Asynchronous_SW
PA14.Signal=SYS_JTCK-SWCLK
PA15.GPIOParameters=GPIO_Label
PA15.GPIO_Label=SPI5_IRQ
PA15.Signal=GPIO_Input
PA2.Mode=MII
PA2.Signal=ETH_MDIO
PA3.Mode=MII
PA3.Signal=ETH_COL
PA4.Signal=COMP_DAC1_group
PA5.GPIOParameters=GPIO_Speed
PA5.GPIO_Speed=GPIO_SPEED_FREQ_HIGH
PA5.Mode=RGB666
PA5.Signal=LTDC_R4
PA6.GPIOParameters=GPIO_Speed
PA6.GPIO_Speed=GPIO_SPEED_FREQ_HIGH
PA6.Mode=RGB666
PA6.Signal=LTDC_G2
PA7.Mode=MII
PA7.Signal=ETH_RX_DV
PA8.GPIOParameters=GPIO_Label
PA8.GPIO_Label=SPI2_IRQ
PA8.Signal=GPIO_Input
PA9.Mode=Activate_VBUS
PA9.Signal=USB_OTG_FS_VBUS
PB0.GPIOParameters=GPIO_Speed
PB0.GPIO_Speed=GPIO_SPEED_FREQ_HIGH
PB0.Mode=RGB666
PB0.Signal=LTDC_R3
PB1.GPIOParameters=GPIO_Speed
PB1.GPIO_Speed=GPIO_SPEED_FREQ_HIGH
PB1.Mode=RGB666
PB1.Signal=LTDC_R6
PB10.Mode=Activate Rx Err signal
PB10.Signal=ETH_RX_ER
PB11.Mode=MII
PB11.Signal=ETH_TX_EN
PB12.Mode=MII
PB12.Signal=ETH_TXD0
PB13.Mode=MII
PB13.Signal=ETH_TXD1
PB14.Mode=Full_Duplex_Master
PB14.Signal=SPI2_MISO
PB15.GPIOParameters=GPIO_Label
PB15.GPIO_Label=TFT_BRIGHTNESS
PB15.Signal=S_TIM12_CH2
PB2.GPIOParameters=GPIO_PuPd,GPIO_Label
PB2.GPIO_Label=NFAULT
PB2.GPIO_PuPd=GPIO_PULLUP
PB2.Signal=GPIO_Input
PB3.Mode=Trace_Asynchronous_SW
PB3.Signal=SYS_JTDO-SWO
PB5.GPIOParameters=GPIO_Label
PB5.GPIO_Label=USER_SW
PB5.Signal=GPIO_Output
PB6.Mode=I2C
PB6.Signal=I2C1_SCL
PB7.Mode=I2C
PB7.Signal=I2C1_SDA
PB8.Mode=MII
PB8.Signal=ETH_TXD3
PB9.GPIOParameters=GPIO_Label
PB9.GPIO_Label=SPI4_IRQ
PB9.Signal=GPIO_Input
PC0.GPIOParameters=GPIO_Speed
PC0.GPIO_Speed=GPIO_SPEED_FREQ_HIGH
PC0.Mode=RGB666
PC0.Signal=LTDC_R5
PC1.Mode=MII
PC1.Signal=ETH_MDC
PC10.GPIOParameters=GPIO_Speed
PC10.GPIO_Speed=GPIO_SPEED_FREQ_HIGH
PC10.Mode=RGB666
PC10.Signal=LTDC_R2
PC11.GPIOParameters=GPIO_PuPd,GPIO_Label
PC11.GPIO_Label=OUT_PAR
PC11.GPIO_PuPd=GPIO_NOPULL
PC11.Signal=GPIO_Output
PC12.Mode=SD_1_bit
PC12.Signal=SDMMC1_CK
PC13.GPIOParameters=GPIO_Label
PC13.GPIO_Label=DIN2
PC13.Signal=GPIO_Input
PC14/OSC32_IN.GPIOParameters=GPIO_Speed,GPIO_Label
PC14/OSC32_IN.GPIO_Label=DOUT1
PC14/OSC32_IN.GPIO_Speed=GPIO_SPEED_FREQ_LOW
PC14/OSC32_IN.Signal=GPIO_Output
PC15/OSC32_OUT.GPIOParameters=GPIO_Label
PC15/OSC32_OUT.GPIO_Label=DOUT2
PC15/OSC32_OUT.Signal=GPIO_Output
PC2.Mode=MII
PC2.Signal=ETH_TXD2
PC3.Mode=MII
PC3.Signal=ETH_TX_CLK
PC4.Mode=MII
PC4.Signal=ETH_RXD0
PC5.Mode=MII
PC5.Signal=ETH_RXD1
PC6.GPIOParameters=GPIO_PuPd,GPIO_Label
PC6.GPIO_Label=ENC_A
PC6.GPIO_PuPd=GPIO_PULLUP
PC6.Signal=S_TIM8_CH1
PC7.GPIOParameters=GPIO_PuPd,GPIO_Label
PC7.GPIO_Label=ENC_B
PC7.GPIO_PuPd=GPIO_PULLUP
PC7.Signal=S_TIM8_CH2
PC8.Mode=SD_1_bit
PC8.Signal=SDMMC1_D0
PC9.GPIOParameters=GPIO_Speed,GPIO_Label
PC9.GPIO_Label=MCLK_25
PC9.GPIO_Speed=GPIO_SPEED_FREQ_VERY_HIGH
PC9.Mode=Clock-out-2
PC9.Signal=RCC_MCO_2
PD0.Signal=FMC_D2_DA2
PD1.Signal=FMC_D3_DA3
PD10.Signal=FMC_D15_DA15
PD11.GPIOParameters=GPIO_Speed,GPIO_Label
PD11.GPIO_Label=SPI2_CSB
PD11.GPIO_Speed=GPIO_SPEED_FREQ_HIGH
PD11.Signal=GPIO_Output
PD12.GPIOParameters=GPIO_Speed,GPIO_Label
PD12.GPIO_Label=SPI2_CSA
PD12.GPIO_Speed=GPIO_SPEED_FREQ_HIGH
PD12.Signal=GPIO_Output
PD13.GPIOParameters=GPIO_PuPd,GPIO_Label
PD13.GPIO_Label=OE_SYNC
PD13.GPIO_PuPd=GPIO_NOPULL
PD13.Signal=GPIO_Output
PD14.Signal=FMC_D0_DA0
PD15.Signal=FMC_D1_DA1
PD2.Mode=SD_1_bit
PD2.Signal=SDMMC1_CMD
PD3.GPIOParameters=GPIO_Speed
PD3.GPIO_Speed=GPIO_SPEED_FREQ_HIGH
PD3.Mode=RGB666
PD3.Signal=LTDC_G7
PD4.GPIOParameters=GPIO_Label
PD4.GPIO_Label=USB_OTG_FS_OC
PD4.Signal=GPIO_Input
PD5.GPIOParameters=GPIO_Label
PD5.GPIO_Label=USB_OTG_FS_PSO
PD5.Signal=GPIO_Output
PD6.GPIOParameters=GPIO_Speed
PD6.GPIO_Speed=GPIO_SPEED_FREQ_HIGH
PD6.Mode=RGB666
PD6.Signal=LTDC_B2
PD7.GPIOParameters=GPIO_Label
PD7.GPIO_Label=IRQ_TOUCH
PD7.Signal=GPIO_Input
PD8.Signal=FMC_D13_DA13
PD9.Signal=FMC_D14_DA14
PE0.Signal=FMC_NBL0
PE1.Signal=FMC_NBL1
PE10.Signal=FMC_D7_DA7
PE11.Signal=FMC_D8_DA8
PE12.Signal=FMC_D9_DA9
PE13.Signal=FMC_D10_DA10
PE14.Signal=FMC_D11_DA11
PE15.Signal=FMC_D12_DA12
PE2.Mode=Full_Duplex_Master
PE2.Signal=SPI4_SCK
PE3.GPIOParameters=GPIO_Speed,GPIO_Label
PE3.GPIO_Label=SPI4_CSA
PE3.GPIO_Speed=GPIO_SPEED_FREQ_HIGH
PE3.Signal=GPIO_Output
PE4.GPIOParameters=GPIO_Speed,GPIO_Label
PE4.GPIO_Label=SPI4_CSB
PE4.GPIO_Speed=GPIO_SPEED_FREQ_HIGH
PE4.Signal=GPIO_Output
PE5.Mode=Full_Duplex_Master
PE5.Signal=SPI4_MISO
PE6.Mode=Full_Duplex_Master
PE6.Signal=SPI4_MOSI
PE7.Signal=FMC_D4_DA4
PE8.Signal=FMC_D5_DA5
PE9.Signal=FMC_D6_DA6
PF0.Signal=FMC_A0
PF1.Signal=FMC_A1
PF10.GPIOParameters=GPIO_Speed
PF10.GPIO_Speed=GPIO_SPEED_FREQ_HIGH
PF10.Mode=RGB666
PF10.Signal=LTDC_DE
PF11.Signal=FMC_SDNRAS
PF12.Signal=FMC_A6
PF13.Signal=FMC_A7
PF14.Signal=FMC_A8
PF15.Signal=FMC_A9
PF2.Signal=FMC_A2
PF3.Signal=FMC_A3
PF4.Signal=FMC_A4
PF5.Signal=FMC_A5
PF6.GPIOParameters=GPIO_Label
PF6.GPIO_Label=SD_DETECT
PF6.Signal=GPIO_Input
PF7.Mode=Full_Duplex_Master
PF7.Signal=SPI5_SCK
PF8.Mode=Full_Duplex_Master
PF8.Signal=SPI5_MISO
PF9.Mode=Full_Duplex_Master
PF9.Signal=SPI5_MOSI
PG0.Signal=FMC_A10
PG1.Signal=FMC_A11
PG10.GPIOParameters=GPIO_Speed
PG10.GPIO_Speed=GPIO_SPEED_FREQ_HIGH
PG10.Mode=RGB666
PG10.Signal=LTDC_G3
PG11.GPIOParameters=GPIO_Speed
PG11.GPIO_Speed=GPIO_SPEED_FREQ_HIGH
PG11.Mode=RGB666
PG11.Signal=LTDC_B3
PG12.GPIOParameters=GPIO_Speed
PG12.GPIO_Speed=GPIO_SPEED_FREQ_HIGH
PG12.Mode=RGB666
PG12.Signal=LTDC_B4
PG13.GPIOParameters=GPIO_Speed,GPIO_Label
PG13.GPIO_Label=SPI5_CSB
PG13.GPIO_Speed=GPIO_SPEED_FREQ_HIGH
PG13.Signal=GPIO_Output
PG14.GPIOParameters=GPIO_Speed,GPIO_Label
PG14.GPIO_Label=SPI5_CSA
PG14.GPIO_Speed=GPIO_SPEED_FREQ_HIGH
PG14.Signal=GPIO_Output
PG15.Signal=FMC_SDNCAS
PG2.GPIOParameters=GPIO_PuPd,GPIO_Label
PG2.GPIO_Label=PWR_DIRECT
PG2.GPIO_PuPd=GPIO_NOPULL
PG2.Signal=GPIO_Output
PG3.GPIOParameters=GPIO_PuPd,GPIO_Label
PG3.GPIO_Label=PWR_SSTART
PG3.GPIO_PuPd=GPIO_NOPULL
PG3.Signal=GPIO_Output
PG4.Signal=FMC_A14_BA0
PG5.Signal=FMC_A15_BA1
PG6.GPIOParameters=GPIO_Speed
PG6.GPIO_Speed=GPIO_SPEED_FREQ_HIGH
PG6.Mode=RGB666
PG6.Signal=LTDC_R7
PG7.GPIOParameters=GPIO_Speed
PG7.GPIO_Speed=GPIO_SPEED_FREQ_HIGH
PG7.Mode=RGB666
PG7.Signal=LTDC_CLK
PG8.Signal=FMC_SDCLK
PG9.GPIOParameters=GPIO_PuPd,GPIO_Label,GPIO_ModeDefaultOutputPP
PG9.GPIO_Label=OUT_SER
PG9.GPIO_ModeDefaultOutputPP=GPIO_MODE_OUTPUT_PP
PG9.GPIO_PuPd=GPIO_NOPULL
PG9.Signal=GPIO_Output
PH0/OSC_IN.Mode=HSE-External-Oscillator
PH0/OSC_IN.Signal=RCC_OSC_IN
PH1/OSC_OUT.Mode=HSE-External-Oscillator
PH1/OSC_OUT.Signal=RCC_OSC_OUT
PH2.Mode=SdramChipSelect1_1
PH2.Signal=FMC_SDCKE0
PH3.Mode=SdramChipSelect1_1
PH3.Signal=FMC_SDNE0
PH4.GPIOParameters=GPIO_Speed
PH4.GPIO_Speed=GPIO_SPEED_FREQ_HIGH
PH4.Mode=RGB666
PH4.Signal=LTDC_G4
PH5.Signal=FMC_SDNWE
PH6.Mode=MII
PH6.Signal=ETH_RXD2
PH7.Mode=MII
PH7.Signal=ETH_RXD3
PI0.GPIOParameters=GPIO_Speed
PI0.GPIO_Speed=GPIO_SPEED_FREQ_HIGH
PI0.Mode=RGB666
PI0.Signal=LTDC_G5
PI1.Mode=Full_Duplex_Master
PI1.Signal=SPI2_SCK
PI10.GPIOParameters=GPIO_Speed
PI10.GPIO_Speed=GPIO_SPEED_FREQ_HIGH
PI10.Mode=RGB666
PI10.Signal=LTDC_HSYNC
PI11.GPIOParameters=GPIO_Speed
PI11.GPIO_Speed=GPIO_SPEED_FREQ_HIGH
PI11.Mode=RGB666
PI11.Signal=LTDC_G6
PI3.Mode=Full_Duplex_Master
PI3.Signal=SPI2_MOSI
PI4.GPIOParameters=GPIO_Label
PI4.GPIO_Label=ENC_SW
PI4.Signal=GPIO_Input
PI5.GPIOParameters=GPIO_Speed
PI5.GPIO_Speed=GPIO_SPEED_FREQ_HIGH
PI5.Mode=RGB666
PI5.Signal=LTDC_B5
PI6.GPIOParameters=GPIO_Speed
PI6.GPIO_Speed=GPIO_SPEED_FREQ_HIGH
PI6.Mode=RGB666
PI6.Signal=LTDC_B6
PI7.GPIOParameters=GPIO_Speed
PI7.GPIO_Speed=GPIO_SPEED_FREQ_HIGH
PI7.Mode=RGB666
PI7.Signal=LTDC_B7
PI8.GPIOParameters=GPIO_Label
PI8.GPIO_Label=DIN1
PI8.Signal=GPIO_Input
PI9.GPIOParameters=GPIO_Speed
PI9.GPIO_Speed=GPIO_SPEED_FREQ_HIGH
PI9.Mode=RGB666
PI9.Signal=LTDC_VSYNC
RCC.HSE_VALUE=25000000
RCC.SYSCLKFreq_VALUE=216000000
RCC.SYSCLKSource=RCC_SYSCLKSOURCE_PLLCLK
board=EEZ H25005 MCU board v0.3

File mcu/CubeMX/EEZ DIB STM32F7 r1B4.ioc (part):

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Mcu.Name=STM32F769IGTx
Mcu.Package=LQFP176
Mcu.UserName=STM32F769IGTx
PA0/WKUP.Mode=MII
PA0/WKUP.Signal=ETH_CRS
PA1.Mode=MII
PA1.Signal=ETH_RX_CLK
PA10.Mode=OTG/Dual_Role_Device
PA10.Signal=USB_OTG_FS_ID
PA11.Mode=OTG/Dual_Role_Device
PA11.Signal=USB_OTG_FS_DM
PA12.Mode=OTG/Dual_Role_Device
PA12.Signal=USB_OTG_FS_DP
PA13.Mode=Trace_Asynchronous_SW
PA13.Signal=SYS_JTMS-SWDIO
PA14.Mode=Trace_Asynchronous_SW
PA14.Signal=SYS_JTCK-SWCLK
PA15.GPIOParameters=GPIO_Label
PA15.GPIO_Label=SPI5_IRQ
PA15.Signal=GPIO_Input
PA2.Mode=MII
PA2.Signal=ETH_MDIO
PA3.Mode=MII
PA3.Signal=ETH_COL
PA4.Signal=COMP_DAC1_group
PA5.GPIOParameters=GPIO_Speed
PA5.GPIO_Speed=GPIO_SPEED_FREQ_HIGH
PA5.Mode=RGB666
PA5.Signal=LTDC_R4
PA6.GPIOParameters=GPIO_Speed
PA6.GPIO_Speed=GPIO_SPEED_FREQ_HIGH
PA6.Mode=RGB666
PA6.Signal=LTDC_G2
PA7.Mode=MII
PA7.Signal=ETH_RX_DV
PA8.GPIOParameters=GPIO_Label
PA8.GPIO_Label=SPI2_IRQ
PA8.Signal=GPIO_Input
PA9.Mode=Activate_VBUS
PA9.Signal=USB_OTG_FS_VBUS
PB0.GPIOParameters=GPIO_Speed
PB0.GPIO_Speed=GPIO_SPEED_FREQ_HIGH
PB0.Mode=RGB666
PB0.Signal=LTDC_R3
PB1.GPIOParameters=GPIO_Speed
PB1.GPIO_Speed=GPIO_SPEED_FREQ_HIGH
PB1.Mode=RGB666
PB1.Signal=LTDC_R6
PB10.Mode=Activate Rx Err signal
PB10.Signal=ETH_RX_ER
PB11.Mode=MII
PB11.Signal=ETH_TX_EN
PB12.Mode=MII
PB12.Signal=ETH_TXD0
PB13.Mode=MII
PB13.Signal=ETH_TXD1
PB14.Mode=Full_Duplex_Master
PB14.Signal=SPI2_MISO
PB15.GPIOParameters=GPIO_Label
PB15.GPIO_Label=TFT_BRIGHTNESS
PB15.Signal=S_TIM12_CH2
PB2.GPIOParameters=GPIO_PuPd,GPIO_Label
PB2.GPIO_Label=NFAULT
PB2.GPIO_PuPd=GPIO_PULLUP
PB2.Signal=GPIO_Input
PB3.Mode=Trace_Asynchronous_SW
PB3.Signal=SYS_JTDO-SWO
PB4.GPIOParameters=GPIO_Label
PB4.GPIO_Label=UART_TX/DOUT1
PB4.Mode=Asynchronous
PB4.Signal=UART7_TX
PB5.GPIOParameters=GPIO_Label
PB5.GPIO_Label=DOUT2
PB5.Signal=GPIO_Output
PB6.Mode=I2C
PB6.Signal=I2C1_SCL
PB7.Mode=I2C
PB7.Signal=I2C1_SDA
PB8.Mode=MII
PB8.Signal=ETH_TXD3
PB9.GPIOParameters=GPIO_Label
PB9.GPIO_Label=SPI4_IRQ
PB9.Signal=GPIO_Input
PC0.GPIOParameters=GPIO_Speed
PC0.GPIO_Speed=GPIO_SPEED_FREQ_HIGH
PC0.Mode=RGB666
PC0.Signal=LTDC_R5
PC1.Mode=MII
PC1.Signal=ETH_MDC
PC10.GPIOParameters=GPIO_Speed
PC10.GPIO_Speed=GPIO_SPEED_FREQ_HIGH
PC10.Mode=RGB666
PC10.Signal=LTDC_R2
PC11.GPIOParameters=GPIO_Label
PC11.GPIO_Label=SD_DETECT
PC11.Signal=GPIO_Input
PC12.Mode=SD_1_bit
PC12.Signal=SDMMC1_CK
PC13.GPIOParameters=GPIO_Label
PC13.GPIO_Label=DIN2
PC13.Signal=GPIO_Input
PC14/OSC32_IN.Mode=LSE-External-Oscillator
PC14/OSC32_IN.Signal=RCC_OSC32_IN
PC15/OSC32_OUT.Mode=LSE-External-Oscillator
PC15/OSC32_OUT.Signal=RCC_OSC32_OUT
PC2.Mode=MII
PC2.Signal=ETH_TXD2
PC3.Mode=MII
PC3.Signal=ETH_TX_CLK
PC4.Mode=MII
PC4.Signal=ETH_RXD0
PC5.Mode=MII
PC5.Signal=ETH_RXD1
PC6.GPIOParameters=GPIO_PuPd,GPIO_Label
PC6.GPIO_Label=ENC_A
PC6.GPIO_PuPd=GPIO_PULLUP
PC6.Signal=S_TIM8_CH1
PC7.GPIOParameters=GPIO_PuPd,GPIO_Label
PC7.GPIO_Label=ENC_B
PC7.GPIO_PuPd=GPIO_PULLUP
PC7.Signal=S_TIM8_CH2
PC8.Mode=SD_1_bit
PC8.Signal=SDMMC1_D0
PC9.GPIOParameters=GPIO_Speed,GPIO_Label
PC9.GPIO_Label=MCLK_25
PC9.GPIO_Speed=GPIO_SPEED_FREQ_VERY_HIGH
PC9.Mode=Clock-out-2
PC9.Signal=RCC_MCO_2
PD0.Signal=FMC_D2_DA2
PD1.Signal=FMC_D3_DA3
PD10.Signal=FMC_D15_DA15
PD11.GPIOParameters=GPIO_Speed,GPIO_Label
PD11.GPIO_Label=SPI2_CSB
PD11.GPIO_Speed=GPIO_SPEED_FREQ_HIGH
PD11.Signal=GPIO_Output
PD12.GPIOParameters=GPIO_Speed,GPIO_Label
PD12.GPIO_Label=SPI2_CSA
PD12.GPIO_Speed=GPIO_SPEED_FREQ_HIGH
PD12.Signal=GPIO_Output
PD13.GPIOParameters=GPIO_PuPd,GPIO_Label
PD13.GPIO_Label=OE_SYNC
PD13.GPIO_PuPd=GPIO_NOPULL
PD13.Signal=GPIO_Output
PD14.Signal=FMC_D0_DA0
PD15.Signal=FMC_D1_DA1
PD2.Mode=SD_1_bit
PD2.Signal=SDMMC1_CMD
PD3.GPIOParameters=GPIO_Speed
PD3.GPIO_Speed=GPIO_SPEED_FREQ_HIGH
PD3.Mode=RGB666
PD3.Signal=LTDC_G7
PD4.GPIOParameters=GPIO_Label
PD4.GPIO_Label=USB_OTG_FS_OC
PD4.Signal=GPIO_Input
PD5.GPIOParameters=GPIO_Label
PD5.GPIO_Label=USB_OTG_FS_PSO
PD5.Signal=GPIO_Output
PD6.GPIOParameters=GPIO_Speed
PD6.GPIO_Speed=GPIO_SPEED_FREQ_HIGH
PD6.Mode=RGB666
PD6.Signal=LTDC_B2
PD7.GPIOParameters=GPIO_Label
PD7.GPIO_Label=IRQ_TOUCH
PD7.Signal=GPIO_Input
PD8.Signal=FMC_D13_DA13
PD9.Signal=FMC_D14_DA14
PE0.Signal=FMC_NBL0
PE1.Signal=FMC_NBL1
PE10.Signal=FMC_D7_DA7
PE11.Signal=FMC_D8_DA8
PE12.Signal=FMC_D9_DA9
PE13.Signal=FMC_D10_DA10
PE14.Signal=FMC_D11_DA11
PE15.Signal=FMC_D12_DA12
PE2.Mode=Full_Duplex_Master
PE2.Signal=SPI4_SCK
PE3.GPIOParameters=GPIO_Speed,GPIO_Label
PE3.GPIO_Label=SPI4_CSA
PE3.GPIO_Speed=GPIO_SPEED_FREQ_HIGH
PE3.Signal=GPIO_Output
PE4.GPIOParameters=GPIO_Speed,GPIO_Label
PE4.GPIO_Label=SPI4_CSB
PE4.GPIO_Speed=GPIO_SPEED_FREQ_HIGH
PE4.Signal=GPIO_Output
PE5.Mode=Full_Duplex_Master
PE5.Signal=SPI4_MISO
PE6.Mode=Full_Duplex_Master
PE6.Signal=SPI4_MOSI
PE7.Signal=FMC_D4_DA4
PE8.Signal=FMC_D5_DA5
PE9.Signal=FMC_D6_DA6
PF0.Signal=FMC_A0
PF1.Signal=FMC_A1
PF10.GPIOParameters=GPIO_Speed
PF10.GPIO_Speed=GPIO_SPEED_FREQ_HIGH
PF10.Mode=RGB666
PF10.Signal=LTDC_DE
PF11.Signal=FMC_SDNRAS
PF12.Signal=FMC_A6
PF13.Signal=FMC_A7
PF14.Signal=FMC_A8
PF15.Signal=FMC_A9
PF2.Signal=FMC_A2
PF3.Signal=FMC_A3
PF4.Signal=FMC_A4
PF5.Signal=FMC_A5
PF6.GPIOParameters=GPIO_Label
PF6.GPIO_Label=UART_RX/DIN1
PF6.Mode=Asynchronous
PF6.Signal=UART7_RX
PF7.Mode=Full_Duplex_Master
PF7.Signal=SPI5_SCK
PF8.Mode=Full_Duplex_Master
PF8.Signal=SPI5_MISO
PF9.Mode=Full_Duplex_Master
PF9.Signal=SPI5_MOSI
PG0.Signal=FMC_A10
PG1.Signal=FMC_A11
PG10.GPIOParameters=GPIO_Speed
PG10.GPIO_Speed=GPIO_SPEED_FREQ_HIGH
PG10.Mode=RGB666
PG10.Signal=LTDC_G3
PG11.GPIOParameters=GPIO_Speed
PG11.GPIO_Speed=GPIO_SPEED_FREQ_HIGH
PG11.Mode=RGB666
PG11.Signal=LTDC_B3
PG12.GPIOParameters=GPIO_Speed
PG12.GPIO_Speed=GPIO_SPEED_FREQ_HIGH
PG12.Mode=RGB666
PG12.Signal=LTDC_B4
PG13.GPIOParameters=GPIO_Speed,GPIO_Label
PG13.GPIO_Label=SPI5_CSB
PG13.GPIO_Speed=GPIO_SPEED_FREQ_HIGH
PG13.Signal=GPIO_Output
PG14.GPIOParameters=GPIO_Speed,GPIO_Label
PG14.GPIO_Label=SPI5_CSA
PG14.GPIO_Speed=GPIO_SPEED_FREQ_HIGH
PG14.Signal=GPIO_Output
PG15.Signal=FMC_SDNCAS
PG2.GPIOParameters=GPIO_PuPd,GPIO_Label
PG2.GPIO_Label=PWR_DIRECT
PG2.GPIO_PuPd=GPIO_NOPULL
PG2.Signal=GPIO_Output
PG3.GPIOParameters=GPIO_PuPd,GPIO_Label
PG3.GPIO_Label=PWR_SSTART
PG3.GPIO_PuPd=GPIO_NOPULL
PG3.Signal=GPIO_Output
PG4.Signal=FMC_A14_BA0
PG5.Signal=FMC_A15_BA1
PG6.GPIOParameters=GPIO_Speed
PG6.GPIO_Speed=GPIO_SPEED_FREQ_HIGH
PG6.Mode=RGB666
PG6.Signal=LTDC_R7
PG7.GPIOParameters=GPIO_Speed
PG7.GPIO_Speed=GPIO_SPEED_FREQ_HIGH
PG7.Mode=RGB666
PG7.Signal=LTDC_CLK
PG8.Signal=FMC_SDCLK
PG9.GPIOParameters=GPIO_PuPd,GPIO_Label,GPIO_ModeDefaultOutputPP
PG9.GPIO_Label=USER_SW
PG9.GPIO_ModeDefaultOutputPP=GPIO_MODE_OUTPUT_PP
PG9.GPIO_PuPd=GPIO_NOPULL
PG9.Signal=GPIO_Output
PH0/OSC_IN.Mode=HSE-External-Oscillator
PH0/OSC_IN.Signal=RCC_OSC_IN
PH1/OSC_OUT.Mode=HSE-External-Oscillator
PH1/OSC_OUT.Signal=RCC_OSC_OUT
PH2.Mode=SdramChipSelect1_1
PH2.Signal=FMC_SDCKE0
PH3.Mode=SdramChipSelect1_1
PH3.Signal=FMC_SDNE0
PH4.GPIOParameters=GPIO_Speed
PH4.GPIO_Speed=GPIO_SPEED_FREQ_HIGH
PH4.Mode=RGB666
PH4.Signal=LTDC_G4
PH5.Signal=FMC_SDNWE
PH6.Mode=MII
PH6.Signal=ETH_RXD2
PH7.Mode=MII
PH7.Signal=ETH_RXD3
PI0.GPIOParameters=GPIO_Speed
PI0.GPIO_Speed=GPIO_SPEED_FREQ_HIGH
PI0.Mode=RGB666
PI0.Signal=LTDC_G5
PI1.Mode=Full_Duplex_Master
PI1.Signal=SPI2_SCK
PI10.GPIOParameters=GPIO_Speed
PI10.GPIO_Speed=GPIO_SPEED_FREQ_HIGH
PI10.Mode=RGB666
PI10.Signal=LTDC_HSYNC
PI11.GPIOParameters=GPIO_Speed
PI11.GPIO_Speed=GPIO_SPEED_FREQ_HIGH
PI11.Mode=RGB666
PI11.Signal=LTDC_G6
PI3.Mode=Full_Duplex_Master
PI3.Signal=SPI2_MOSI
PI4.GPIOParameters=GPIO_Label
PI4.GPIO_Label=ENC_SW
PI4.Signal=GPIO_Input
PI5.GPIOParameters=GPIO_Speed
PI5.GPIO_Speed=GPIO_SPEED_FREQ_HIGH
PI5.Mode=RGB666
PI5.Signal=LTDC_B5
PI6.GPIOParameters=GPIO_Speed
PI6.GPIO_Speed=GPIO_SPEED_FREQ_HIGH
PI6.Mode=RGB666
PI6.Signal=LTDC_B6
PI7.GPIOParameters=GPIO_Speed
PI7.GPIO_Speed=GPIO_SPEED_FREQ_HIGH
PI7.Mode=RGB666
PI7.Signal=LTDC_B7
PI9.GPIOParameters=GPIO_Speed
PI9.GPIO_Speed=GPIO_SPEED_FREQ_HIGH
PI9.Mode=RGB666
PI9.Signal=LTDC_VSYNC
RCC.HSE_VALUE=25000000
RCC.SYSCLKFreq_VALUE=216000000
RCC.SYSCLKSource=RCC_SYSCLKSOURCE_PLLCLK
board=EEZ H25005 MCU board v0.3
